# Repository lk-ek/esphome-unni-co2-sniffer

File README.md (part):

<!-- SPDX-FileCopyrightText: 2026 The esphome-unni-co2-sniffer contributors -->
<!-- SPDX-License-Identifier: GPL-3.0-or-later -->

# Unni CO₂ Smartification and Sensirion Gadget Bridge

ESPHome components and example firmware for two related sensor integrations:

- a Seeed Studio XIAO ESP32-C3 added to an Unni CO₂ monitor without taking control away from the original electronics; and
- a stationary, externally powered AHT21 room sensor, optionally combined with an ENS160, which reuses the same Sensirion/MyAmbience BLE and persistent-history implementation.

In the Unni build, the XIAO ESP32-C3 acts primarily as a **passive sniffer**:

- CO₂ is decoded from the existing I²C traffic between the Unni controller and the CO₂ module.
- Temperature and relative humidity are reconstructed from the existing RT/RH timing signals.
- Measurements are exposed to Home Assistant through ESPHome.
- The same measurements can be advertised over BLE in a Sensirion MyAmbience-compatible format.
- Optional persistent BLE history allows historical samples to be downloaded with MyAmbience.

The tested Unni monitor is sold as **CO2 Monitor Carbon Dioxide Detector 0601**, hence the orchestrator component name. BLE and history are provided by the separate reusable bridge:

```yaml
sensirion_gadget_bridge:
  id: unni_sensirion_bridge
  profile: trh_co2
  device_name: "Unni CO2 Monitor"

co2_monitor_0601:
  sensirion_bridge_id: unni_sensirion_bridge
```

The Unni integration was developed against one specific hardware revision. Other revisions should be verified before connecting the ESP.

---

## Supported devices

### Unni monitor

The passive in-monitor integration provides:

- passively decoded CO₂ concentration;
- reconstructed temperature and relative humidity;
- battery voltage and estimated battery state of charge;
- USB/VBUS presence;
- automatic USB/battery power policy and Light Sleep; and
- optional diagnostics and raw capture.

### Standalone room sensor

The stationary, externally powered integration provides:

- AHT21 temperature and relative humidity;
- optional ENS160 TVOC and AQI as Home Assistant-only air-quality measurements;
- SHT43-compatible BLE live data and persistent history; and
- no battery, VBUS or Unni capture subsystem.

ENS160 eCO₂ is deliberately not published. It is an algorithmic estimate, not the direct CO₂ measurement required by the `trh_co2` profile.

### Shared integrations

- ESPHome / Home Assistant
- Sensirion-compatible BLE live advertisements
- persistent BLE history with MyAmbience-compatible GATT download

### Unni-only power management

The following features belong to the Unni/XIAO integration:

- automatic distinction between USB and battery operation
- ESP32-C3 dynamic frequency scaling
- automatic Light Sleep in battery mode
- reduced BLE advertising rate on battery
- reduced Home Assistant publication rate on battery
- optional `Energy Save Mode` for measuring battery-style firmware behavior while physically powered through USB
- dedicated BLE-only measurement build without Wi-Fi or Home Assistant

### Unni diagnostics

Optional debug builds provide:

- RT/RH timing diagnostics
- I²C framing and decoder diagnostics
- raw I²C captures
- VCD conversion tools
- recovery diagnostics for occasionally missed GPIO edges

---

# Unni monitor integration

Everything in this section concerns the passive XIAO ESP32-C3 installation in
the Unni monitor or its future ESP32-C6 replacement PCB. The standalone room
sensor is documented separately below.

## ESP32-C6 Rev A PCB — work in progress

The [`unni-smartification-c6/`](unni-smartification-c6/) subtree contains a
dedicated four-layer ESP32-C6 hardware design with a replacement USB/power board
and a separate ESP/battery board. It keeps the original Unni connections as
T-taps and adds autonomous charging, USB/battery source isolation, native USB
and a hardware-inhibited forced-awake 5 V path.

> [!WARNING]
> This PCB is a **work in progress**. Placement and routing are not final, and
> the design has not replaced the currently tested XIAO ESP32-C3 installation.
> Reproducible schematic, connectivity, mechanical and system-level SPICE checks
> reduce design risk but do not constitute assembled-hardware validation.

The prototype PCBs for this project are kindly sponsored by
[PCBWay](https://www.pcbway.com/). Thank you to PCBWay for supporting the
project and helping turn the design into physical prototypes.

See the [ESP32-C6 Rev A project README](unni-smartification-c6/README.md) for
the power architecture, mechanics, current routing/fabrication status and
validation commands.

## XIAO ESP32-C3 wiring

| XIAO | GPIO | Unni connection | Purpose |
|---|---:|---|---|
| D1 | GPIO3 | RT | temperature timing signal |
| D2 | GPIO4 | RH | humidity timing signal |
| D4 | GPIO6 | CO₂ SDA | passive I²C data sniffing |
| D5 | GPIO7 | CO₂ SCL | passive I²C clock sniffing |
| D0 | GPIO2 / ADC1_CH2 | battery-divider midpoint | battery voltage |
| D3 | GPIO5 | VBUS-divider midpoint | USB power detection |
| 5V | — | Unni VBUS / 5 V | ESP supply |
| GND | — | Unni GND / battery − | common ground |

`RT` and `RH` are the PCB points associated with the temperature and humidity measurement circuitry.

The ESP must remain electrically passive with respect to the original signal paths.

The current tested installation uses **10 kΩ series resistors on each passive ESP tap**:

```text
Unni signal ---- 10 kΩ ---- XIAO GPIO
```

The resistors belong only in the ESP branches; do not insert them into the original Unni signal path. The RT/RH calibration is hardware-dependent, so calibration data collected with earlier direct or three/four-wire tap arrangements must not be mixed with the current two-wire/10 kΩ setup.

The RT/RH decoder now keeps separate temperature views: a diagnostic RT-model temperature, a dedicated Unni LCD-emulation curve, and a provisional external-reference Air Temperature curve. RH uses the RH-phase carrier period normalized by REF with temperature compensation. Air Temperature is the canonical temperature exported through Sensirion BLE/history when it is inside its validated envelope; the RT model is retained as a fallback outside that envelope. See `co2_monitor_0601/calibration.h` and the dated calibration notes under `docs/history/` for the coefficients and fit provenance.

---

## Battery voltage measurement

The tested circuit uses two 1 MΩ resistors:

```text
Battery + --- 1 MΩ ---+--- D0 / GPIO2
                      |
                     1 MΩ
                      |
Battery − / GND ------+

D0 / GPIO2 --- 0.1 µF --- GND
```

This produces a divider ratio of 2.0.

The firmware uses ESP-IDF ADC calibration, averaging and 12 dB attenuation.

Battery-related entities include:

- `Battery Voltage`
- `Battery Level`
- `Battery Runtime Estimate`
- `Battery Charge Time Estimate`
- `Battery Discharge Rate` (`%/h`, diagnostic when `debug_metrics: true`)
- `Battery Charge Rate` (`%/h`, diagnostic when `debug_metrics: true`)

`Battery Level` is a voltage-based Li-ion estimate. It is intentionally unavailable while physical USB power is present because charger-driven battery voltage is not a useful open-circuit state-of-charge measurement.

Debug builds intentionally limit the native ESPHome API to one simultaneous client while raw UDP capture is enabled. Home Assistant should keep that slot; use USB serial for live `esphome logs`. Additional native API log clients can consume enough heap on the ESP32-C3 to starve lwIP. If UDP export sees sustained `ENOMEM` pressure, the affected debug capture is dropped after repeated failures instead of retrying indefinitely and holding memory/network resources.

The runtime and charge-time estimates are learned from the observed voltage trend rather than from a fixed assumed current draw. Each USB/battery transition starts a new rate-estimator session, followed by a two-minute settling period. The short-term estimator then uses at least a five-minute observation window and exponentially smooths subsequent rate measurements. Until a meaningful trend is available, the corresponding estimate remains unavailable instead of publishing a speculative value.

Battery runtime also has a persistent self-learning layer. During battery operation the component accumulates real elapsed time and voltage-derived SOC drop. Once a session contains at least 2 hours and 8 percentage points of discharge, it can estimate an equivalent full-runtime value. A completed qualifying battery session is folded into the persistent model with a conservative EMA (25% new session / 75% previous model). The active session and learned model are checkpointed to flash every `battery_learning_save_interval` (default `30min`) and on session completion, so an overnight run or reboot does not discard the calibration data. The production `Battery Runtime Estimate` blends the persistent model with the recent discharge-rate estimate; before a learned model exists it behaves like the original recent-rate estimator.

With `debug_metrics: true`, `Battery Learned Full Runtime`, `Battery Learning Progress`, and `Battery Learning Cycles` expose the learning state. `Battery Learning Progress` reaches 100% when the current session has both at least 2 hours of data and at least 8 percentage points of SOC drop. The model intentionally learns effective runtime rather than claiming to measure true battery capacity in mAh; without a coulomb counter the voltage/SOC curve cannot provide that measurement reliably.

Battery-learning flash writes are logged after a successful synchronous commit.
Periodic checkpoints are labeled `periodic`, OTA-triggered force-saves are
labeled `OTA`, and end-of-session commits are labeled `session-end`, together
with the persisted SOC/session runtime/progress and learned-runtime state.

On battery, the estimator uses the normal voltage-derived SOC curve. With USB present, `Battery Level` stays unavailable and the charge estimator uses the charger-influenced battery-node voltage only as a charge-progress proxy. The charge ETA is therefore inherently less accurate, especially in the constant-voltage/taper region near full charge.

---

## USB/VBUS detection

The tested VBUS divider is:

```text
VBUS / 5 V --- 220 kΩ ---+--- D3 / GPIO5
                         |
                        220 kΩ
                         |
                        GND
```

The physical state is exposed as:

```text
USB Power
```

The reported value always reflects actual VBUS presence, even when the firmware is deliberately using the battery power policy through `Energy Save Mode`.

---

# Unni installation

## Minimal configuration

A minimal normal configuration is:

```yaml
esphome:
  name: i2csniffer

external_components:
  - source:
      type: local
      path: .

esp32:
  board: seeed_xiao_esp32c3
  framework:
    type: esp-idf

wifi:
  ssid: !secret wifi_ssid
  password: !secret wifi_password

api:
  encryption:
    key: !secret i2csniffer__encryption_key

sensirion_gadget_bridge:
  id: unni_sensirion_bridge
  profile: trh_co2

co2_monitor_0601:
  sensirion_bridge_id: unni_sensirion_bridge
```

The repository contains complete example configurations, so in normal use it is easier to start with one of those rather than build the YAML from scratch.

Build or flash with ESPHome:

```bash
esphome compile i2c-sniffer.yaml
esphome run i2c-sniffer.yaml
```

# Unni build variants

The repository contains these configurations for the Unni monitor:

| Configuration | Wi-Fi / HA | BLE | Debug capture | Purpose |
|---|---|---|---|---|
| `i2c-sniffer.yaml` | yes | yes | no | normal operation |
| `i2c-sniffer-debug.yaml` | yes | yes | yes | protocol/debugging work |
| `i2c-sniffer-no-ble.yaml` | yes | no | no | BLE power comparison |
| `i2c-sniffer-ble-only.yaml` | no | yes | no | BLE-only power measurement |
| `i2c-sniffer-sht43-probe.yaml` | yes | experimental | no | MyAmbience reverse engineering |

The SHT43 probe is diagnostic firmware and should not be used as the normal
Unni device identity.

---

# Unni Home Assistant entities

Home Assistant support is enabled by default:

```yaml
co2_monitor_0601:
  home_assistant: true
```

Omitting `home_assistant` is equivalent to setting it to `true`.

Only the dedicated BLE-only build intentionally uses:

```yaml
co2_monitor_0601:
  home_assistant: false
```

In that build the local ESPHome entity objects remain registered internally so ESPHome 2026.8 can derive its entity-vector sizes correctly, but the supplied YAML contains no `wifi:` or `api:` component, so they are not exposed to Home Assistant and cause no network traffic.

The normal `i2c-sniffer.yaml` build intentionally exposes only the production
measurement set plus operational power/battery controls:

The default Home Assistant names are intentionally concise: the physical-air `air_temperature` entity is shown as `Temperature`, and the physical carrier-based `rh_humidity` entity as `Humidity`.

- `CO2`
- `Temperature` (physical-air estimate)
- `Humidity` (physical carrier-based estimate)
- `Battery Voltage`
- `Battery Level`
- `Battery Runtime Estimate`
- `Battery Charge Time Estimate`
- `USB Power`
- `Energy Save Mode`
- `WiFi Home Assistant` when the runtime connectivity control is enabled
- `BLE Privacy` and `BLE Pairing Mode` while the experimental secure MyAmbience settings support is enabled

Sensor definitions may be customized:

```yaml
co2_monitor_0601:
  co2:
    name: "Living Room CO2"

  air_temperature:
    name: "Temperature"

  rh_humidity:
    name: "Humidity"
```

The shipped `i2c-sniffer-debug.yaml` sets `debug_metrics: true` and creates the
complete entity set as well: `RT Temperature`, both `Unni Display ...`
emulation entities, protocol error counters, raw timing/ratio metrics, battery
charge/discharge rates, quality and calibration/extrapolation flags. These are
not instantiated by the normal build.

# Unni component configuration

Useful options include:

```yaml
co2_monitor_0601:
  # Home Assistant
  home_assistant: true
  ha_publish_interval: 60s

  # Bridge composition and battery-specific BLE interval
  sensirion_bridge_id: unni_sensirion_bridge
  ble_battery_advertising_interval: 3s

  # Power management
  light_sleep: true
  light_sleep_max_awake: 10s
  co2_wake_idle_stable: 500ms
  co2_wake_guard_time: 500ms
  energy_save_mode_default: false
  energy_save_grace: 3s

  # Hardware
  rt_pin: 3
  rh_pin: 4
  co2_sda_pin: 6
  co2_scl_pin: 7
  battery_pin: 2
  battery_divider_ratio: 2.0
  battery_update_interval: 60s
  battery_learning_save_interval: 30min
  usb_power_pin: 5

  # Startup
  sniffer_start_delay: 10s

  # Diagnostics
  debug_metrics: false
  # Compiles main-loop stage timing and heap telemetry into the firmware.
  runtime_diagnostics: false
  # Optional ESP32-C3/C6 hardware assist. "gpio" keeps the pure ISR backend;
  # "rmt_scl" records SCL in RMT hardware and uses it only to repair strictly
  # protocol-invalid GPIO captures.
  i2c_capture_backend: gpio
  debug_capture: false
  # Experimental only: temporarily becomes an I2C master on a long-idle
  # LOW/LOW CO2 bus, using only the ESP32-C3 internal pull-ups through the
  # external 10 kOhm tap resistors.
  active_i2c_probe: false
  active_i2c_probe_interval: 60s
```

The defaults match the tested XIAO ESP32-C3 installation.

All configured GPIOs must be unique.

`rtrh_enabled`, `rtrh_edge_capture`, and `rtrh_decode_only` are mutually
exclusive capture modes. `rtrh_gpio_setup: true` is accepted only with one of
those modes; invalid combinations fail during YAML validation rather than
retrying GPIO setup at runtime.

`battery_pin` must be an ESP32-C3 ADC1-capable GPIO.

The Unni orchestrator configures its ESP-IDF power-management requirements;
the bridge configures the BLE server and persistent-history partition.

`active_i2c_probe` is intentionally disabled by default. It is a hardware diagnostic, not normal passive-sniffer operation. The probe runs only on battery policy after the CO2 bus has remained LOW/LOW and edge-free for at least one second. It first tries `0xEC05`; if no slave ACKs, it tries the observed `0x21B1` start command. Every attempt restores SDA/SCL to input-only/no-pull mode immediately afterwards. Do not enable it without series resistance on both CO2 tap lines.

---

# Unni USB and battery power policy

The firmware uses different runtime policies depending on physical power.

## USB power

Normal USB operation prioritizes responsiveness and reliability:

- automatic MCU Light Sleep is prevented
- CPU frequency is held at 80 MHz
- Wi-Fi power saving is disabled at runtime with `WIFI_PS_NONE`
- CO₂ I²C capture remains continuously enabled
- valid CO₂ measurements are published immediately
- valid RT temperature is published immediately; RH is published when its carrier timing also validates
- BLE advertisements use the USB interval, default `2s`

Because USB power is available, reducing ESP consumption is not the priority in this mode.

## Battery power

Battery operation prioritizes low average power:

- automatic Light Sleep is enabled
- GPIO3/GPIO4 RT/RH activity wakes the ESP
- CPU frequency is temporarily raised to 80 MHz while measurements are captured
- during a powered CO₂ measurement window the passive sniffer is active; after two plausible CO₂ observations it is gated off before the sensor rail collapses
- the expected slow SCL/SDA shutdown decay is ignored with the I²C interrupts disabled, avoiding large garbage captures and ISR storms
- after the dead bus has remained LOW/LOW for `co2_wake_idle_stable` (default `500ms`) plus `co2_wake_guard_time` (default `500ms`), GPIO7/SCL HIGH is armed as the next CO₂ power-up wake source
- a real CO₂ power-up disarms GPIO7 wake and re-enables the passive sniffer before the native measurement transaction; GPIO6 remains passive
- after the RT/RH wake window is complete, the ESP may return to Light Sleep
- Wi-Fi uses `WIFI_PS_MIN_MODEM`
- Home Assistant publication is throttled to the latest values, default once per minute
- BLE advertisements use the battery interval, default `3s`

The corresponding options are:

```yaml
sensirion_gadget_bridge:
  id: unni_sensirion_bridge
  advertising_interval: 2s

co2_monitor_0601:
  sensirion_bridge_id: unni_sensirion_bridge
  light_sleep: true
  light_sleep_max_awake: 10s
  co2_wake_idle_stable: 500ms
  co2_wake_guard_time: 500ms
  ha_publish_interval: 60s
  ble_battery_advertising_interval: 3s
```

---

# Unni Energy Save Mode

`Energy Save Mode` exists mainly for controlled power measurements.

When enabled while the hardware is still physically powered from USB, the component behaves as if USB power were absent.

This allows a USB power meter to compare normal firmware behavior against the battery-oriented runtime policy without changing the electrical power source.

The physical `USB Power` entity remains truthful.

In Energy Save Mode:

- automatic Light Sleep is enabled
- the battery capture-window policy is used
- Wi-Fi uses `WIFI_PS_MIN_MODEM`
- BLE uses the battery advertising interval
- Home Assistant publication uses the battery throttle

The default is:

```yaml
co2_monitor_0601:
  energy_save_mode_default: false
  energy_save_grace: 3s
```

The grace period keeps the normal USB power locks briefly after the HA switch is enabled so that the state change can propagate before automatic Light Sleep becomes active.

Native USB Serial/JTAG may become unavailable while automatic Light Sleep is active. This does not affect the ESP32-C3 ROM USB bootloader, so USB flashing remains possible.

---

# Unni BLE-only measurement build

`i2c-sniffer-ble-only.yaml` is intended for measuring the cost of BLE without Wi-Fi/API overhead.

It intentionally contains no:

- `wifi:`
- `api:`
- captive portal
- OTA

It keeps:

- sensor decoding
- BLE live data
- BLE history
- power management

The relevant configuration is:

```yaml
sensirion_gadget_bridge:
  id: unni_sensirion_bridge
  profile: trh_co2
  ble: true
  ble_live: true
  ble_history: true

co2_monitor_0601:
  sensirion_bridge_id: unni_sensirion_bridge
  home_assistant: false
  energy_save_mode_default: true
  energy_save_grace: 0s
```

Flash this build over USB.

Recent example measurements on the tested hardware were approximately:

| Mode | Average power |
|---|---:|
| normal Wi-Fi + HA + BLE | 2.84 mW |
| Energy Save Mode | 2.07 mW |
| BLE-only | 1.34 mW |

These measurements were made with a USB power meter and should be treated as comparative rather than laboratory-grade absolute values.

Avoid running `ping`, `esphome logs`, an actively polling web UI or other unnecessary network traffic during power measurements.

---

# Standalone room sensor integration

This is a stationary, externally powered AHT21 room sensor. An ENS160 may be
fitted for additional Home Assistant air-quality data. The existing
`mobilesensor-*.yaml` filenames are retained for compatibility, but “mobile
sensor” is not used here as the device description because the hardware has no
battery operating mode.

It uses `sensirion_gadget_bridge` directly and does not instantiate
`co2_monitor_0601`. Consequently it has no Unni GPIO capture, battery ADC,
battery learning, VBUS detection, Energy Save Mode or automatic Light-Sleep
policy.

## Hardware

The shipped configurations target `wemos_d1_mini32` and use one 100 kHz I²C
bus:

| GPIO | Device | Address | Purpose |
|---:|---|---:|---|
| GPIO23 | AHT21 and optional ENS160 | `0x38` / `0x53` | SDA |
| GPIO19 | AHT21 and optional ENS160 | `0x38` / `0x53` | SCL |

No battery divider, VBUS input or Unni signal tap is part of this configuration.

## Configuration

```yaml
sensirion_gadget_bridge:
  id: sensirion_bridge
  profile: sht43_trh
  temperature_id: aht21_temp
  humidity_id: aht21_humi
  history_time_id: room_sensor_wall_clock
  ble: true
  ble_live: true
  ble_history: true
  advertising_interval: 2s
```

Use `mobilesensor-sensirion.yaml` when an ENS160 is fitted, or
`mobilesensor-sensirion-no-ens160.yaml` for AHT21-only hardware. Both variants
provide the same AHT21 BLE identity, live data, persistent history, OTA flush
and MyAmbience GATT behavior.

The bridge coalesces sequential AHT21 temperature and humidity callbacks for
100 ms. A restarted coalescing window publishes the newest complete pair rather
than two partially updated samples.

## Home Assistant and ENS160

Both variants expose AHT21 temperature and humidity. The ENS160 variant also
exposes TVOC, AQI and an `ENS160` control switch. It starts off after every
boot. Enabling it wakes the sensor before polling resumes; disabling it suspends
polling before Deep Sleep and publishes TVOC/AQI as unavailable.

AHT21 compensation remains enabled for ENS160 operation. Heating from an active
ENS160 may influence the nearby AHT21; no unvalidated correction curve is
applied. TVOC and AQI never participate in BLE sample completeness, GATT or
history. ENS160 eCO₂ is exposed nowhere. Switching the ENS160 on or off cannot
pause, clear or reset AHT21 history.

---

# Shared Sensirion bridge

## Architecture and sample ownership

BLE and history consume one authoritative, profile-aware sample owned by
`sensirion_gadget_bridge`:

```yaml
sensirion_gadget_bridge:
  id: unni_sensirion_bridge
  profile: trh_co2       # or sht43_trh
  ble: true
  ble_live: true
  ble_history: true
  device_name: "Unni CO2 Monitor"
  identity_mode: device_derived
  advertising_interval: 2s
  history_time_id: unni_wall_clock
```

For `sht43_trh`, `temperature_id` and `humidity_id` may bind the bridge directly
to ESPHome sensors. They must be configured together.
`sht43_identity_probe: true` remains a compatibility alias for this profile;
contradictory profile and alias settings are rejected.

| Concern | Unni monitor | Standalone room sensor |
|---|---|---|
| Measurement producer | passive CO₂ and RT/RH decoders | AHT21 state callbacks |
| Bridge profile | `trh_co2` | `sht43_trh` |
| Complete sample | finite T/RH plus valid CO₂ | finite T/RH; CO₂ remains unset |
| History guard | Unni capture-aware guard | generic transfer watchdogs only |
| Optional air quality | none | ENS160 TVOC/AQI in HA only |
| Power policy | USB/battery orchestration | externally powered; no Unni policy |

Invalid or out-of-range input does not replace the last valid sample. BLE live
data, SHT43 GATT temperature/humidity and history all read the same accepted
sample, preventing different paths from applying different completeness rules.
The first complete sample is immediately eligible for history; subsequent
samples follow the configured history interval. Existing flash layout and GATT
history wire format are shared by both producers.

## Sensirion / MyAmbience compatibility

The normal Unni firmware advertises temperature, humidity and CO₂ in a Sensirion Gadget/MyAmbience-compatible format. The standalone room-sensor profile advertises SHT43-style temperature and humidity only.
For the temperature field it uses `Air Temperature` inside the externally validated air-temperature envelope, falling back to the diagnostic RT model only when that physical-air estimate is unavailable. BLE humidity remains the physical carrier-based `RH Humidity`; the Unni display-emulation values are never advertised as physical measurements.

The reusable bridge is composed with the Unni orchestrator in the shipped BLE
YAMLs. The name shown for the normal MyCO2 gadget is configured on that bridge:

```yaml
sensirion_gadget_bridge:
  id: unni_sensirion_bridge
  profile: trh_co2
  device_name: "Unni CO2 Monitor"

co2_monitor_0601:
  sensirion_bridge_id: unni_sensirion_bridge
```

`device_name` defaults to `Unni CO2 Monitor` for the `trh_co2` profile and to `SHT43 DB` for the `sht43_trh` profile. It is limited to 31 bytes to match the Sensirion `AlternativeDeviceName` characteristic. It sets the normal Device Information model name and the default `AlternativeDeviceName`. A name explicitly changed through the Device Settings service remains persistent. The compatibility-sensitive GAP/local identity remains `S` and is intentionally not changed by this option. The old `ble_device_name` key remains on the Unni compatibility surface.

Bridge `identity_mode` defaults to `device_derived` and therefore needs no YAML
configuration. It derives a stable, locally administered Bluetooth address and
Device ID from the ESP eFuse MAC so multiple monitors do not collide.
`legacy_fixed` remains available only as an explicit compatibility override for
installations that must retain the old fixed identity. Changing identity can
invalidate existing bonds and MyAmbience caches and may require opening Pairing
Mode once in Home Assistant.

The GAP name used by the normal compatibility mode is:

```text
S
```

The Device Information Service identifies the manufacturer as:

```text
Gadget
```

The firmware does not claim that the hardware was manufactured by Sensirion.

The BLE compatibility implementation is local code using ESPHome and ESP-IDF BLE APIs. The production firmware does not directly vendor or link the Sensirion Gadget BLE Arduino Library or Sensirion UPT Core.

Parts of the protocol implementation were developed with reference to Sensirion's published software. See:

- [THIRD_PARTY_NOTICES.md](THIRD_PARTY_NOTICES.md)
- `LICENSES/`

for attribution, provenance and upstream license texts.

---

## Persistent BLE history

Advertising after GATT disconnects is reasserted deterministically so ESPHome's automatic advertiser restart cannot replace the Sensirion manufacturer-data payload. The Device Settings privacy flag (`IsAdvertiseDataEnabled`) is persistent and is logged explicitly at startup.

With:

```yaml
sensirion_gadget_bridge:
  ble_history: true
```

samples are stored in the `senshist` flash partition.

MyAmbience can download the history through the compatible GATT protocol.

The history ring is persistent across normal reboots.

The 4096-sample history is flash-backed. Only a small pending write ring is kept in RAM, so enabling MyAmbience history does not require a second 32 KiB in-memory copy of the persistent sample store. When a continuous run exceeds 4096 samples, the sparse time anchor advances with each ring eviction; restored history therefore still timestamps the retained 4096-sample window rather than the already-overwritten beginning of the run.

History metadata uses a redundant version-4 A/B journal in the first and last
sectors of the 64 KiB partition; the 14 data sectors and 8-byte sample wire
layout are unchanged. Version-2/3 metadata is read in place and migrated on the
next metadata flush. V4 uses the two formerly reserved metadata words for a
sparse wall-clock anchor and the sample count of the newest continuous run. The
anchor is created only when a run starts after a reboot/cadence gap, when the
wall clock first becomes valid, or after a material wall-clock correction; it is
not stored per sample. API-enabled variants obtain UTC from Home Assistant. The
BLE-only build has no wall-clock source and therefore starts a new relative run
after reboot rather than inventing timestamps. Failed metadata writes remain
dirty and are retried. A client may select only intervals from 60 seconds
through 24 hours. Changing the interval clears history incrementally from the
main loop (at most one sector erase per loop), while sampling and download
remain paused.

The official Sensirion download format has one header with one interval and one
`age-of-latest-sample`, so it cannot describe gaps inside a single transfer.
The bridge therefore keeps runs separate on the wire. The first download sends
the newest continuous run (or its newest requested subset). Each subsequently
completed download within a rolling five-minute session sends the next older
continuous run; completion resets the five-minute timer. Disconnecting does not
reset the cursor, while an aborted transfer does not advance it. Once the timer
expires, the next download starts again at the newest run. The history-count
characteristic follows the same cursor so MyAmbience sees the size of the run it
will receive next.

Completed-run boundaries are persisted sparsely in ESPHome NVS: one 8-byte
record per gap containing the run's UTC anchor, sample count and physical flash
start slot. No timestamp is added to ordinary samples and the Sensirion sample
or download wire formats are unchanged. Up to 128 completed-run descriptors are
retained; descriptors whose samples have already fallen out of the 4096-sample
flash window are ignored. Runs without a trustworthy wall-clock anchor are not
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
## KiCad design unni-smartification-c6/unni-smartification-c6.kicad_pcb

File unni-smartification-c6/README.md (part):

# Unni CO2 Smartification — ESP32-C6 Rev A

Target: **KiCad 10.99 nightly or newer**. The current manufacturing master uses a 4-layer stackup and native KiCad 10.99 geometric constraints.

This repository contains two physical PCBs in one KiCad PCB file so cross-board connectivity remains visible while routing. Placement and routing are still work in progress; the schematic and power architecture are substantially defined and covered by reproducible connectivity/SPICE checks.

## PCB sponsorship

The prototype PCBs for this project are kindly sponsored by [PCBWay](https://www.pcbway.com/). A big thank-you to PCBWay for supporting the project and helping turn the design into real hardware.

## Hardware overview

The images below are generated directly from the current KiCad project with `kicad-cli`; they are not hand-maintained screenshots. The two physical boards intentionally remain in one PCB file during design so their interconnect nets can be routed and validated together.

### PCB — component side

The long, narrow board on the left is the **USB / power board**. The larger board on the right is the **ESP / battery board**. The USB board carries the forced-awake 5 V power stage and the enclosure-specific USB interface, while the ESP board carries the charger, 3.3 V supply, ESP32-C6 and the sensor/control interfaces.

For placement and routing inspection, the orthographic top view is also useful:

### PCB — back side

The USB-C receptacle is deliberately a **back-side component** because the mechanical measurements describe the rear side of the original enclosure. Only the measured 19 x 18 mm rear clearance area may contain back-side components; the rest of that board lies against the enclosure. A footprint without an installed 3D model will naturally not appear in these renders even though its pads and board placement are present in KiCad.

### Schematics

#### USB, forced-awake boost and Unni power interface

#### ESP32-C6, charger, 3.3 V regulator and auxiliary interfaces

The simulation harness is intentionally not shown here because it is not part of the manufactured hardware. Its generated image remains available at `docs/images/schematic/simulation-harness.png` for debugging.

### Power sequencing and source handover

There are two independent questions in the power architecture: **how the ESP stays alive**, and **whether the Unni is being fed 5 V so that it behaves as USB-powered rather than entering its battery energy-save mode**.

**1. USB disconnected, normal battery operation.** The protected 1S Li-ion feeds `+BATT`. The discrete load-share path connects the battery to `SYS`, and the TPS63031 generates the regulated `+3V3` rail for the ESP32-C6. The Unni can continue to run from its own battery/DC input without needing the ESP-generated 5 V path. This is the low-power baseline state.

**2. ESP requests forced-awake operation while USB is absent.** Once the ESP is alive from `+3V3`, it may assert `BOOST_CMD`. The hardware-enable network then allows the TPS613222A 5 V boost stage on the USB/power board to run from `+BATT`. Its `+5V` output reaches `UNNI_AC` through the output Schottky diode. Electrically, the Unni now sees the same AC/VBUS-style 5 V condition it would see from USB, so firmware can deliberately pull the Unni out of its battery energy-save behavior.

**3. Real USB is plugged in.** `VBUS` immediately supplies `SYS` through the Schottky/load-share path, so the TPS63031 and ESP are powered from USB rather than discharging the cell. In parallel, the MCP73831 charges `+BATT` at the resistor-programmed current, and the ESP can observe `CHARGE_STAT` as well as the filtered `USB_ADC` divider. USB VBUS also feeds `UNNI_AC` directly through its own Schottky path.

**4. USB always wins over the battery-generated 5 V path.** The forced-awake boost has a hardware VBUS inhibit. When real `VBUS` is present, the MOSFET inhibit network prevents the TPS613222A path from being enabled even if firmware leaves `BOOST_CMD` asserted or crashes in the wrong state. The two 5 V sources therefore do not intentionally drive each other. The output diodes provide the final source isolation at `UNNI_AC`.

**5. USB is removed again.** The charger stops, the battery load-share path retakes `SYS`, and the TPS63031 keeps the ESP on `+3V3` across the source transition. The forced-awake 5 V rail remains off unless firmware explicitly requests it after USB has disappeared. This separation is important: keeping the ESP alive does not automatically force the Unni into its higher-power USB mode.

The practical state table is therefore:

| External USB | `BOOST_CMD` | ESP source | Unni `UNNI_AC` | Result |
| --- | --- | --- | --- | --- |
| absent | 0 | battery -> `SYS` -> TPS63031 | no ESP-generated 5 V | normal battery / energy-save capable |
| absent | 1 | battery -> `SYS` -> TPS63031 | TPS613222A -> `+5V` -> diode | forced-awake / USB-like Unni power state |
| present | 0 | VBUS -> `SYS` -> TPS63031 | VBUS -> diode | USB-powered; battery charging |
| present | 1 | VBUS -> `SYS` -> TPS63031 | VBUS -> diode; boost hardware-inhibited | same safe USB-powered state |

The ADC paths (`BAT_ADC`, `USB_ADC`, `BACKLIGHT_ADC`) and `CHARGE_STAT` let firmware distinguish these power states without making the safety-critical source arbitration depend on software alone.

### Re-generating the README images

With a KiCad 10.99 nightly `kicad-cli` on `PATH`, run:

```sh
./tools/render_readme_assets.sh
```

Or point it at a specific build:

```sh
KICAD_CLI=/path/to/kicad-cli ./tools/render_readme_assets.sh
```

This refreshes all PCB renders and schematic PNGs under `docs/images/`.

## Physical boards

- **USB / power board** — 19 mm fixed width, 1.0 mm finished-board target, USB-C on B.Cu at the measured enclosure datum. It contains USB-C/CC, the TPD2E009DBZR USB ESD shunt, the battery-driven 5 V forced-awake boost and the Unni AC/DC interface.
- **ESP / battery board** — maximum 46 x 32 mm. It contains the ESP32-C6-MINI-1, MCP73831 charger and USB/battery load sharing, TPS63031 3.3 V buck-boost, battery/USB/backlight ADCs, battery NTC, CO2/RT/RH taps, touch emulation, and local service controls.

The boards currently use JST-PH connectors where serviceability is useful. If enclosure clearance proves too tight, their exposed through-hole/SMT pads are also suitable for direct wire soldering; this is an assembly fallback, not a separate electrical architecture.

The 3-pin auxiliary connector **J5** is ordered **pin 1 = `CONN_TOUCH`, pin 2 = `CONN_LED+`, pin 3 = `CONN_BTN`**. `CONN_BTN` goes to ESP32-C6 IO22 (module pin 28); the touch-emulation path couples Q10 to `CONN_TOUCH` through populated C32 = 220 pF.

## Power architecture

```text
USB VBUS ──────────────┬─ MCP73831 (≈196 mA, RPROG=5.1k) ── +BATT
                       ├─ Schottky ── SYS ── TPS63031 ── +3V3 ── ESP32-C6
                       └─ Schottky ─────────────────────── UNNI_AC

protected 1S Li-ion ─ +BATT ─ PMOS load share ─────────── SYS
                    └ +BATT ─ boost switch ─ TPS613222A ─ +5V ─ Schottky ─ UNNI_AC
```

Hardware VBUS inhibit prevents the battery 5 V boost from being enabled while real USB power is present. The battery pack used by the design contains its own protection PCB.

## USB

- USB-C sink: independent 5.1 kΩ Rd on CC1 and CC2.
- Native ESP32-C6 USB Full-Speed is routed through 22 Ω series resistors near the ESP.
- USB ESD: **TI TPD2E009DBZR**, a two-line ground-referenced shunt device with no VBUS/VCC rail. This avoids a clamp path that could back-power VBUS and interfere with the hardware boost inhibit.
- `USB_ADC` includes local RC filtering.
- USB differential geometry is intentionally **not final yet**. Route it only after the selected PCBWay stackup is loaded; final impedance geometry should be checked against PCBWay's impedance/stackup data if controlled impedance is ordered.

## 4-layer PCBWay stackup

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
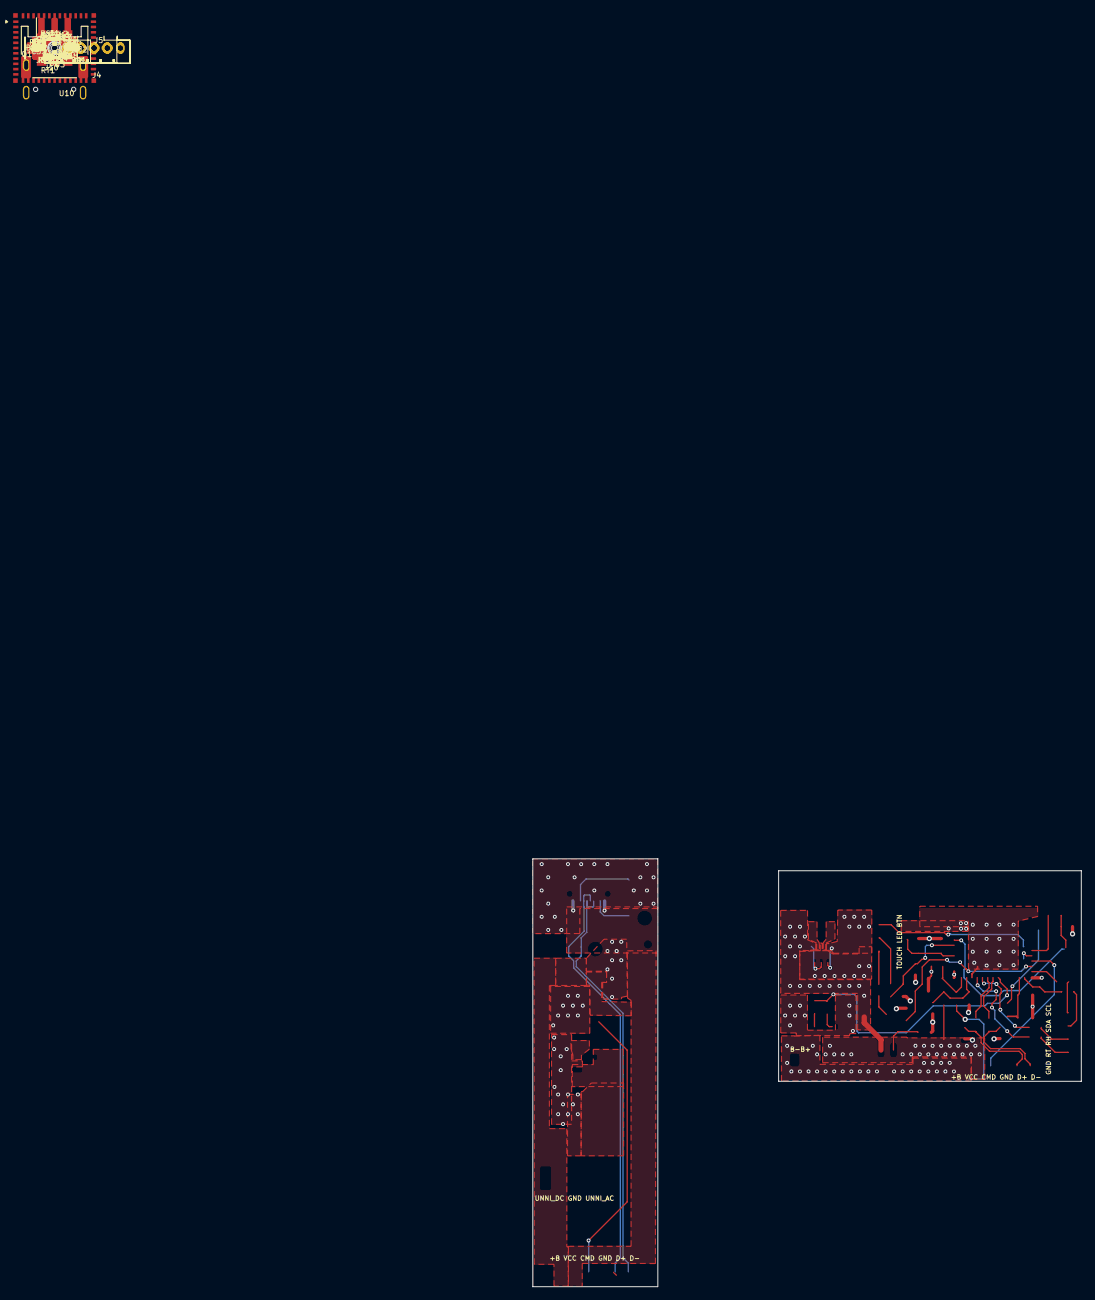
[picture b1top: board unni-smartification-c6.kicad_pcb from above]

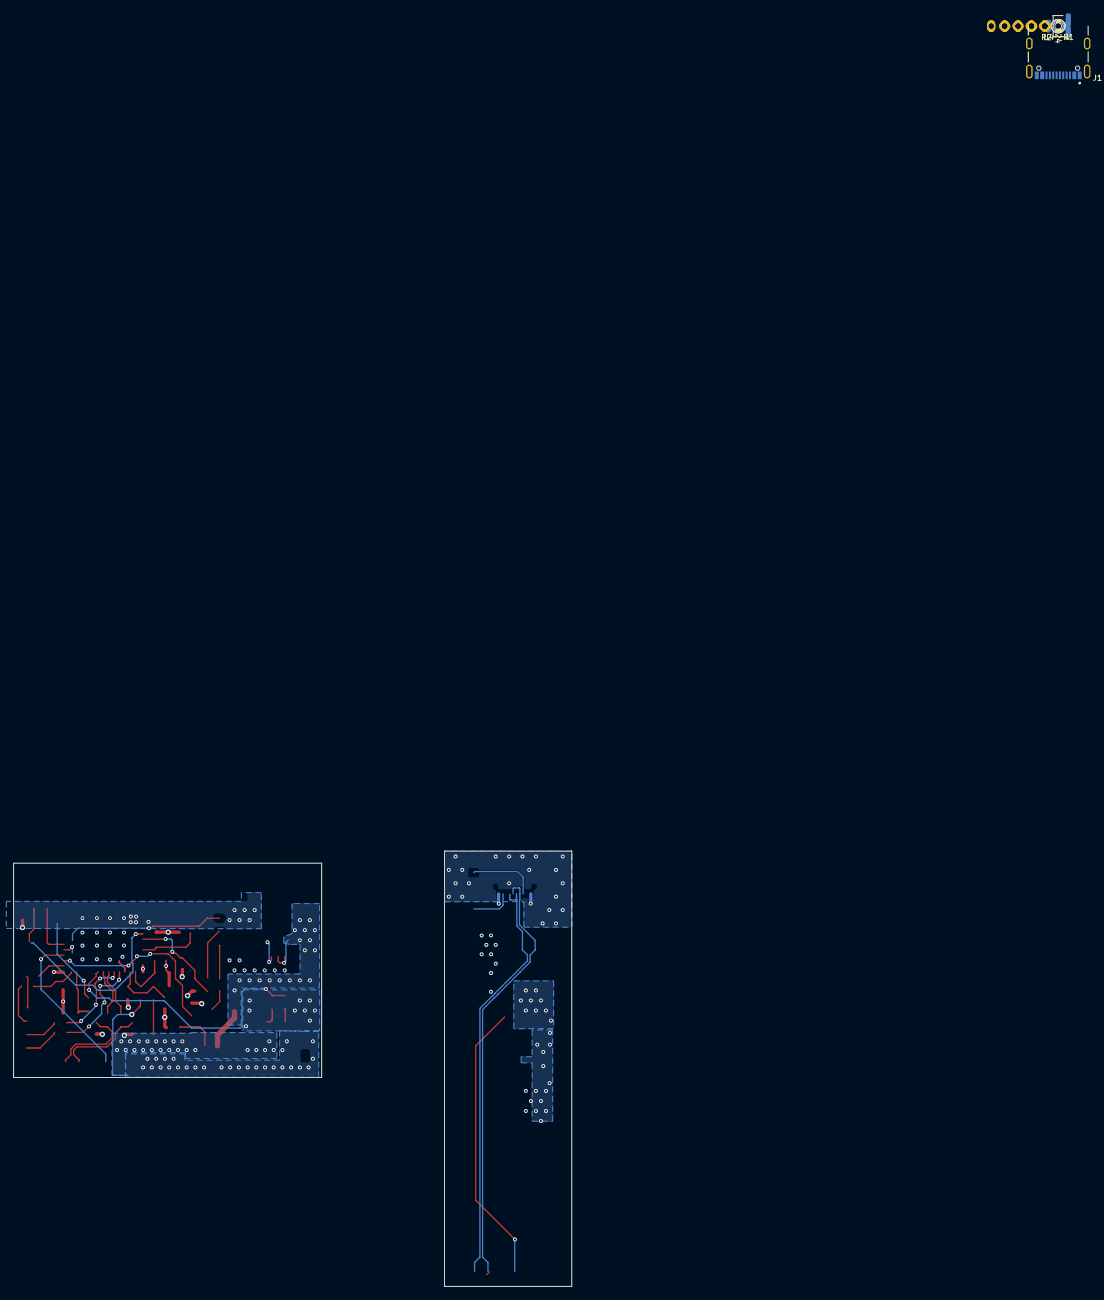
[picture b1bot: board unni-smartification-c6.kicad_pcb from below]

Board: 4 copper layers, 75 parts (5 on the bottom side), 45 nets.

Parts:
C1, C2: 4.7uF; C_0805_2012Metric_Pad1.18x1.45mm_HandSolder
C3, C5, C6, C7: 10uF; C_0805_2012Metric_Pad1.18x1.45mm_HandSolder
C4, C11, C20, C21, C22: 100nF; C_0603_1608Metric_Pad1.08x0.95mm_HandSolder
C8: 22uF; C_0805_2012Metric_Pad1.18x1.45mm_HandSolder
C9: 1uF; C_0603_1608Metric_Pad1.08x0.95mm_HandSolder
C10: 10uF; C_0603_1608Metric_Pad1.08x0.95mm_HandSolder
C12, C13: 22pF DNP; C_0603_1608Metric_Pad1.08x0.95mm_HandSolder
C32: 220pF; C_0603_1608Metric_Pad1.08x0.95mm_HandSolder
C33: 10nF DNP; C_0603_1608Metric_Pad1.08x0.95mm_HandSolder
D1, D3, D4: SS14; D_SMA_Handsoldering
H1: NPTH_2mm; USB_LEFT_MOUNT_D2.0
H2: NPTH_1mm; USB_LEFT_SMALL_D1.0
H3: NPTH_2mm; USB_CENTER_MOUNT_D2.0
H4: NPTH_1.5mm; USB_RIGHT_HOLE_D1.5
J1: UJ20-C-H-G-SMT-1-P16-TR; SAMESKY_UJ20-C-H-G-SMT-1-P16-TR
J2: B2B-PH-K-S; JST_PH_B2B-PH-K_1x02_P2.00mm_Vertical
J3, J10: B6B-PH-K-S; JST_PH_B6B-PH-K_1x06_P2.00mm_Vertical
J4: S3B-PH-SM4-TB; JST_PH_S3B-PH-SM4-TB_1x03-1MP_P2.00mm_Horizontal
J5: B3B-PH-K-S; JST_PH_B3B-PH-K_1x03_P2.00mm_Vertical
J6: B5B-PH-K-S; JST_PH_B5B-PH-K_1x05_P2.00mm_Vertical
L1: 2.2uH; L_Murata_LQH3NPN_3.0x3.0mm_HandSolder
L2: 2.2uH; L_Murata_DFE322520FD_3.2x2.5mm_HandSolder
Q1, Q2: AO3401A; SOT-23_Handsoldering
Q3, Q4, Q10: AO3400A; SOT-23_Handsoldering
R1, R2, R3: 5.1k; R_0805_2012Metric_Pad1.20x1.40mm_HandSolder
R5, R52: 100k; R_0805_2012Metric_Pad1.20x1.40mm_HandSolder
R6, R7, R9, R30, R31: 1M; R_0805_2012Metric_Pad1.20x1.40mm_HandSolder
R8, R20, R21, R34: 10k; R_0805_2012Metric_Pad1.20x1.40mm_HandSolder
R11: 150k; R_0805_2012Metric_Pad1.20x1.40mm_HandSolder
R12, R32, R33, R51: 220k; R_0805_2012Metric_Pad1.20x1.40mm_HandSolder
R13: 47k; R_0805_2012Metric_Pad1.20x1.40mm_HandSolder
R22, R23: 22R; R_0805_2012Metric_Pad1.20x1.40mm_HandSolder
R24: 10K; R_0603_1608Metric_Pad0.98x0.95mm_HandSolder
R40, R41, R42, R43: 10k; R_0603_1608Metric_Pad0.98x0.95mm_HandSolder
R50: 330k; R_0805_2012Metric_Pad1.20x1.40mm_HandSolder
RT1: NTCC-10K; JST_PH_B2B-PH-K_1x02_P2.00mm_Vertical
SW1: RST; SW_Jianfu_TVAF36-N014JW-R_HandSolder
SW2: BOOT; SW_Jianfu_TVAF36-N014JW-R_HandSolder
U1: MCP73831; SOT-23-5_HandSoldering
U2: TPS63031; WSON-10-1EP_2.5x2.5mm_P0.5mm_EP1.2x2mm
U3: TPS613222ADBV; SOT-23-5
U4: TPD2E009DBZR; SOT-23_Handsoldering
U10: ESP32-C6-MINI-1-N4; ESP32-C6-MINI-1

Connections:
+3V3: C5.1, C6.1, C10.1, C11.1, R20.1, R21.1, U2.1 (VOUT), U2.10 (FB), U10.3 (3V3)
+5V: C8.1, D4.2 (A), U3.4 (VOUT)
+BATT: C2.1, J2.2, J3.6, J4.1, J10.6, Q1.3 (D), Q2.2 (S), R7.2, R30.1, U1.3 (V_{BAT})
/ESP32-C6 + Auxiliary/BOOT_GPIO9: R21.2, SW2.2, U10.23 (IO9)
/ESP32-C6 + Auxiliary/ESP_EN: R20.2, SW1.2, U10.8 (EN)
/ESP32-C6 + Auxiliary/USB_N: R22.1, U10.17 (IO12)
/ESP32-C6 + Auxiliary/USB_P: R23.1, U10.18 (IO13)
/USB + Power/BOOST_IN: C7.1, L2.1, Q2.3 (D)
BACKLIGHT_ADC: C33.1, R50.2, R51.1, U10.6 (IO3)
BAT_ADC: C20.1, R30.2, R31.1, U10.12 (IO0)
BAT_TEMP_ADC: C21.1, R34.2, RT1.1, U10.5 (IO2)
BAT_TEMP_EXCITE: R34.1, U10.29 (IO23)
BOOST_CMD: J3.4, J10.4, R8.1, U10.27 (IO21)
CHARGE_STAT: R11.2, R12.1, U10.19 (IO14)
CO2_SCL: R41.2, U10.25 (IO19)
CO2_SDA: R40.2, U10.24 (IO18)
CONN_BTN: J5.3, R24.2
CONN_LED+: J5.2, R50.1
CONN_RH: J6.3, R43.1
CONN_RT: J6.4, R42.1
CONN_SCL: J6.1, R41.1
CONN_SDA: J6.2, R40.1
CONN_TOUCH: C32.1, J5.1
GND: C1.2, C2.2, C3.2, C4.2, C5.2, C6.2, C7.2, C8.2, C9.2, C10.2, C11.2, C12.2, C13.2, C20.2, C21.2, C22.2, C33.2, J1.A1_B12 (GND), J1.B1_A12 (GND__1), J1.SH1 (SHIELD), J1.SH2 (SHIELD__1), J1.SH3 (SHIELD__2), J1.SH4 (SHIELD__3), J2.1, J3.3, J4.2, J6.5, J10.3, Q3.2 (S), Q4.2 (S), Q10.2 (S), R1.2, R2.2, R3.2, R6.1, R9.2, R12.2, R13.1, R31.2, R33.2, R51.2, R52.2, RT1.2, SW1.1, SW2.1, U1.2 (V_{SS}), U2.3 (PGND), U2.7 (PS/SYNC), U2.9 (GND), U2.11 (PGND), U3.2 (GND), U4.3 (GND), U10.1 (GND), U10.2 (GND), U10.11 (GND), U10.14 (GND), U10.36 (GND), U10.37 (GND), U10.38 (GND), U10.39 (GND), U10.40 (GND), U10.41 (GND), U10.42 (GND), U10.43 (GND), U10.44 (GND), U10.45 (GND), U10.46 (GND), U10.47 (GND), U10.48 (GND), U10.49 (GND), U10.50 (GND), U10.51 (GND), U10.52 (GND), U10.53 (GND)
unnamed: J1.A5 (CC1), R1.1
unnamed: J1.B5 (CC2), R2.1
unnamed: Q1.1 (G), R5.2, R6.2
unnamed: Q2.1 (G), Q3.3 (D), R7.1
unnamed: Q3.1 (G), Q4.3 (D), R8.2, R9.1
unnamed: C32.2, Q10.3 (D)
unnamed: R3.1, U1.5 (PROG)
unnamed: R11.1, U1.1 (STAT)
unnamed: L1.1, U2.4 (L1)
unnamed: L1.2, U2.2 (L2)
unnamed: L2.2, U3.1 (SW)
unnamed: R24.1, U10.28 (IO22)
RH: R43.2, U10.16 (IO7)
RT: R42.2, U10.15 (IO6)
SYS: C3.1, C4.1, D1.1 (K), Q1.2 (S), U2.5 (VIN), U2.6 (EN), U2.8 (VINA)
TOUCH_TRIGGER: Q10.1 (G), R52.1, U10.26 (IO20)
UNNI_AC: C9.1, D3.1 (K), D4.1 (K), J4.3
USB_ADC: C22.1, R32.2, R33.1, U10.13 (IO1)
USB_RAW_N: C12.1, J1.A7 (DN1), J1.B7 (DN2), J3.2, J10.2, R22.2, U4.2 (D-)
USB_RAW_P: C13.1, J1.A6 (DP1), J1.B6 (DP2), J3.1, J10.1, R23.2, U4.1 (D+)
VBUS: C1.1, D1.2 (A), D3.2 (A), J1.A4_B9 (VBUS), J1.B4_A9 (VBUS__1), J3.5, J10.5, Q4.1 (G), R5.1, R13.2, R32.1, U1.4 (V_{DD})

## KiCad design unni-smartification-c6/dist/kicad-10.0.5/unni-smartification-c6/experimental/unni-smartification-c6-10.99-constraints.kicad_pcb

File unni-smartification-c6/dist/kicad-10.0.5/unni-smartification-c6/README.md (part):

# Unni CO2 Smartification — ESP32-C6 Rev A

Target: **KiCad 10.99 nightly or newer**. The current manufacturing master uses a 4-layer stackup and native KiCad 10.99 geometric constraints.

This repository contains two physical PCBs in one KiCad PCB file so cross-board connectivity remains visible while routing. Placement and routing are still work in progress; the schematic and power architecture are substantially defined and covered by reproducible connectivity/SPICE checks.

## Hardware overview

The images below are generated directly from the current KiCad project with `kicad-cli`; they are not hand-maintained screenshots. The two physical boards intentionally remain in one PCB file during design so their interconnect nets can be routed and validated together.

### PCB — component side

The long, narrow board on the left is the **USB / power board**. The larger board on the right is the **ESP / battery board**. The USB board carries the forced-awake 5 V power stage and the enclosure-specific USB interface, while the ESP board carries the charger, 3.3 V supply, ESP32-C6 and the sensor/control interfaces.

For placement and routing inspection, the orthographic top view is also useful:

### PCB — back side

The USB-C receptacle is deliberately a **back-side component** because the mechanical measurements describe the rear side of the original enclosure. Only the measured 19 x 18 mm rear clearance area may contain back-side components; the rest of that board lies against the enclosure. A footprint without an installed 3D model will naturally not appear in these renders even though its pads and board placement are present in KiCad.

### Schematics

#### USB, forced-awake boost and Unni power interface

#### ESP32-C6, charger, 3.3 V regulator and auxiliary interfaces

The simulation harness is intentionally not shown here because it is not part of the manufactured hardware. Its generated image remains available at `docs/images/schematic/simulation-harness.png` for debugging.

### Power sequencing and source handover

There are two independent questions in the power architecture: **how the ESP stays alive**, and **whether the Unni is being fed 5 V so that it behaves as USB-powered rather than entering its battery energy-save mode**.

**1. USB disconnected, normal battery operation.** The protected 1S Li-ion feeds `+BATT`. The discrete load-share path connects the battery to `SYS`, and the TPS63031 generates the regulated `+3V3` rail for the ESP32-C6. The Unni can continue to run from its own battery/DC input without needing the ESP-generated 5 V path. This is the low-power baseline state.

**2. ESP requests forced-awake operation while USB is absent.** Once the ESP is alive from `+3V3`, it may assert `BOOST_CMD`. The hardware-enable network then allows the TPS613222A 5 V boost stage on the USB/power board to run from `+BATT`. Its `+5V` output reaches `UNNI_AC` through the output Schottky diode. Electrically, the Unni now sees the same AC/VBUS-style 5 V condition it would see from USB, so firmware can deliberately pull the Unni out of its battery energy-save behavior.

**3. Real USB is plugged in.** `VBUS` immediately supplies `SYS` through the Schottky/load-share path, so the TPS63031 and ESP are powered from USB rather than discharging the cell. In parallel, the MCP73831 charges `+BATT` at the resistor-programmed current, and the ESP can observe `CHARGE_STAT` as well as the filtered `USB_ADC` divider. USB VBUS also feeds `UNNI_AC` directly through its own Schottky path.

**4. USB always wins over the battery-generated 5 V path.** The forced-awake boost has a hardware VBUS inhibit. When real `VBUS` is present, the MOSFET inhibit network prevents the TPS613222A path from being enabled even if firmware leaves `BOOST_CMD` asserted or crashes in the wrong state. The two 5 V sources therefore do not intentionally drive each other. The output diodes provide the final source isolation at `UNNI_AC`.

**5. USB is removed again.** The charger stops, the battery load-share path retakes `SYS`, and the TPS63031 keeps the ESP on `+3V3` across the source transition. The forced-awake 5 V rail remains off unless firmware explicitly requests it after USB has disappeared. This separation is important: keeping the ESP alive does not automatically force the Unni into its higher-power USB mode.

The practical state table is therefore:

| External USB | `BOOST_CMD` | ESP source | Unni `UNNI_AC` | Result |
| --- | --- | --- | --- | --- |
| absent | 0 | battery -> `SYS` -> TPS63031 | no ESP-generated 5 V | normal battery / energy-save capable |
| absent | 1 | battery -> `SYS` -> TPS63031 | TPS613222A -> `+5V` -> diode | forced-awake / USB-like Unni power state |
| present | 0 | VBUS -> `SYS` -> TPS63031 | VBUS -> diode | USB-powered; battery charging |
| present | 1 | VBUS -> `SYS` -> TPS63031 | VBUS -> diode; boost hardware-inhibited | same safe USB-powered state |

The ADC paths (`BAT_ADC`, `USB_ADC`, `BACKLIGHT_ADC`) and `CHARGE_STAT` let firmware distinguish these power states without making the safety-critical source arbitration depend on software alone.

### Re-generating the README images

With a KiCad 10.99 nightly `kicad-cli` on `PATH`, run:

```sh
./tools/render_readme_assets.sh
```

Or point it at a specific build:

```sh
KICAD_CLI=/path/to/kicad-cli ./tools/render_readme_assets.sh
```

This refreshes all PCB renders and schematic PNGs under `docs/images/`.

## Physical boards

- **USB / power board** — 19 mm fixed width, 1.0 mm finished-board target, USB-C on B.Cu at the measured enclosure datum. It contains USB-C/CC, the TPD2E009DBZR USB ESD shunt, the battery-driven 5 V forced-awake boost and the Unni AC/DC interface.
- **ESP / battery board** — maximum 46 x 32 mm. It contains the ESP32-C6-MINI-1, MCP73831 charger and USB/battery load sharing, TPS63031 3.3 V buck-boost, battery/USB/backlight ADCs, battery NTC, CO2/RT/RH taps, touch emulation, and local service controls.

The boards currently use JST-PH connectors where serviceability is useful. If enclosure clearance proves too tight, their exposed through-hole/SMT pads are also suitable for direct wire soldering; this is an assembly fallback, not a separate electrical architecture.

The 3-pin auxiliary connector **J5** is ordered **pin 1 = `CONN_TOUCH`, pin 2 = `CONN_LED+`, pin 3 = `CONN_BTN`**. `CONN_BTN` goes to ESP32-C6 IO22 (module pin 28); the touch-emulation path couples Q10 to `CONN_TOUCH` through populated C32 = 220 pF.

## Power architecture

```text
USB VBUS ──────────────┬─ MCP73831 (≈196 mA, RPROG=5.1k) ── +BATT
                       ├─ Schottky ── SYS ── TPS63031 ── +3V3 ── ESP32-C6
                       └─ Schottky ─────────────────────── UNNI_AC

protected 1S Li-ion ─ +BATT ─ PMOS load share ─────────── SYS
                    └ +BATT ─ boost switch ─ TPS613222A ─ +5V ─ Schottky ─ UNNI_AC
```

Hardware VBUS inhibit prevents the battery 5 V boost from being enabled while real USB power is present. The battery pack used by the design contains its own protection PCB.

## USB

- USB-C sink: independent 5.1 kΩ Rd on CC1 and CC2.
- Native ESP32-C6 USB Full-Speed is routed through 22 Ω series resistors near the ESP.
- USB ESD: **TI TPD2E009DBZR**, a two-line ground-referenced shunt device with no VBUS/VCC rail. This avoids a clamp path that could back-power VBUS and interfere with the hardware boost inhibit.
- `USB_ADC` includes local RC filtering.
- USB differential geometry is intentionally **not final yet**. Route it only after the selected PCBWay stackup is loaded; final impedance geometry should be checked against PCBWay's impedance/stackup data if controlled impedance is ordered.

## 4-layer PCBWay stackup

The KiCad stackup now models PCBWay's published regular 4-layer **1.0 mm / 1 oz outer / 1 oz inner** construction (70% inner-layer residual-copper variant):

| Layer | KiCad model |
| --- | --- |
| F.Cu | 0.035 mm finished Cu (1 oz) |
| dielectric 1 | 0.1855 mm 7628 RC46% prepreg, εr 4.74 |
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
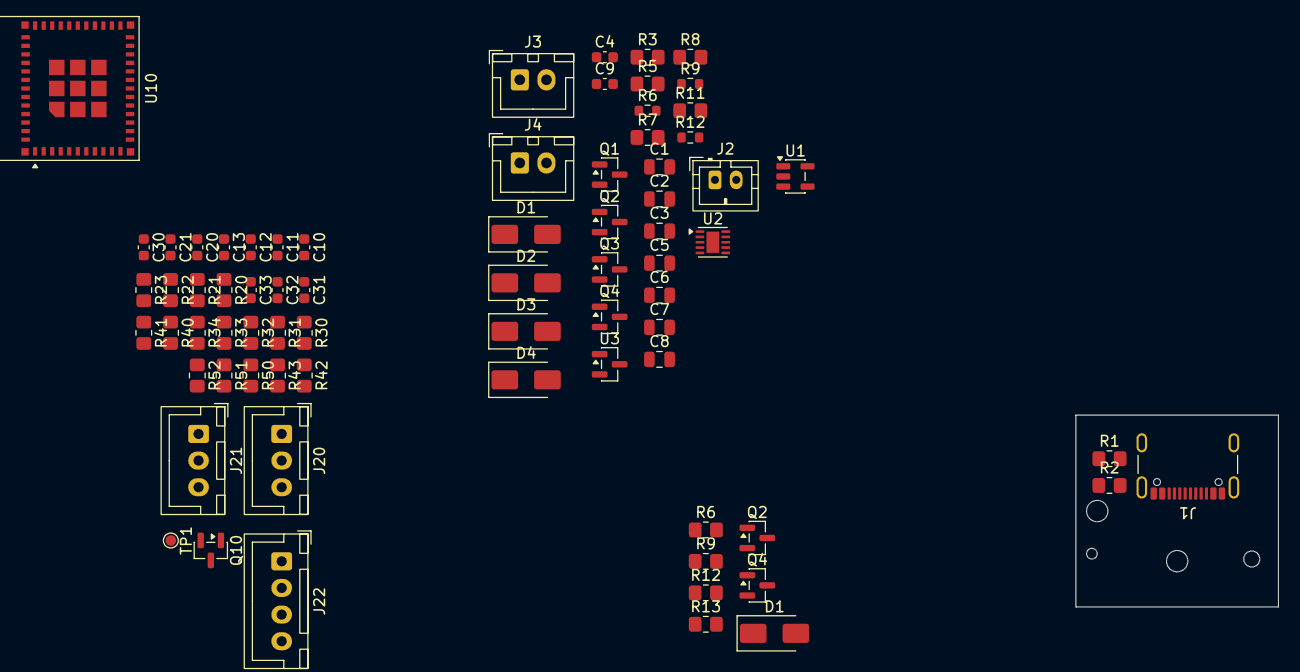
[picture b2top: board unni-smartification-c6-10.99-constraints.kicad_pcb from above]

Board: 2 copper layers, 19.0 x 18.0 mm, 77 parts (0 on the bottom side), 42 nets, no tracks yet.

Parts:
C1, C2: 4.7uF; C_0805_2012Metric
C3, C5, C6, C7: 10uF; C_0805_2012Metric
C4, C11, C20, C21: 100nF; C_0603_1608Metric
C8: 22uF; C_0805_2012Metric
C9: 1uF; C_0603_1608Metric
C10: 10uF; C_0603_1608Metric
C12, C13: 22pF DNP; C_0603_1608Metric
C30: 47pF DNP; C_0603_1608Metric
C31: 100pF DNP; C_0603_1608Metric
C32: 220pF; C_0603_1608Metric
C33: 10nF DNP; C_0603_1608Metric
D1, D1#2, D3, D4: SS14; D_SMA
D2: SS14 DNP; D_SMA
H1: NPTH_2mm; USB_LEFT_MOUNT_D2.0
H2: NPTH_1mm; USB_LEFT_SMALL_D1.0
H3: NPTH_2mm; USB_CENTER_MOUNT_D2.0
H4: NPTH_1.5mm; USB_RIGHT_HOLE_D1.5
J1: UJ20-C-H-G-SMT-1-P16-TR; USB_C_Receptacle_GCT_USB4105-xx-A_16P_TopMnt_Horizontal
J2: B2B-PH-K-S; JST_PH_B2B-PH-K_1x02_P2.00mm_Vertical
J3: B6B-PH-K-S; JST_XH_B2B-XH-A_1x02_P2.50mm_Vertical
J4: S3B-PH-SM4-TB; JST_XH_B2B-XH-A_1x02_P2.50mm_Vertical
J20: CO2 tap: SDA/SCL/GND; JST_XH_B3B-XH-A_1x03_P2.50mm_Vertical
J21: RT/RH tap: RT/RH/GND; JST_XH_B3B-XH-A_1x03_P2.50mm_Vertical
J22: TOUCH / LED+ / LED- / GND; JST_XH_B4B-XH-A_1x04_P2.50mm_Vertical
Q1, Q2, Q2#2: AO3401A; SOT-23
Q3, Q4, Q4#2, Q10: AO3400A; SOT-23
R1, R2, R3: 5.1k; R_0805_2012Metric_Pad1.20x1.40mm_HandSolder
R5, R52: 100k; R_0805_2012Metric_Pad1.20x1.40mm_HandSolder
R6, R9: 1M; R_0603_1608Metric
R6#2, R7, R9#2, R30, R31: 1M; R_0805_2012Metric_Pad1.20x1.40mm_HandSolder
R8, R20, R21, R34, R40, R41, R42, R43: 10k; R_0805_2012Metric_Pad1.20x1.40mm_HandSolder
R11: 150k; R_0805_2012Metric_Pad1.20x1.40mm_HandSolder
R12, R32, R33, R51: 220k; R_0805_2012Metric_Pad1.20x1.40mm_HandSolder
R12#2: 220k; R_0603_1608Metric
R13: 47k; R_0805_2012Metric_Pad1.20x1.40mm_HandSolder
R22, R23: 22R; R_0805_2012Metric_Pad1.20x1.40mm_HandSolder
R50: 330k; R_0805_2012Metric_Pad1.20x1.40mm_HandSolder
TP1: BACKLIGHT_LED_NEG; TestPoint_Pad_D1.0mm
U1: MCP73831; SOT-23-5
U2: TPS63031; WSON-10-1EP_2.5x2.5mm_P0.5mm_EP1.2x2mm
U3: TPS613222A; SOT-23
U10: ESP32-C6-MINI-1-N4; ESP32-C6-MINI-1

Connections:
+3V3: C5.1, C6.1, C10.1, C11.1, R20.1, R21.1, U2.1 (VOUT), U2.10 (FB), U10.3 (3V3)
+5V: C8.1, D2.1 (K), D4.2 (A), U3.1 (VOUT)
+BATT: C2.1, J2.1, J4.1, Q1.3 (D), Q2.2 (S), Q2#2.2 (S), R7.1, R30.1, U1.3 (V_{BAT})
/ESP32-C6 + Auxiliary/BOOT_GPIO9: R21.2, U10.23 (IO9)
/ESP32-C6 + Auxiliary/ESP_EN: R20.2, U10.8 (EN)
/ESP32-C6 + Auxiliary/USB_N: R22.1, U10.17 (IO12)
/ESP32-C6 + Auxiliary/USB_P: R23.1, U10.18 (IO13)
/USB + Power/BOOST_IN: C7.1, Q2.3 (D), Q2#2.3 (D)
BACKLIGHT_ADC: C33.1, R50.2, R51.1, U10.6 (IO3)
BAT_ADC: C20.1, R30.2, R31.1, U10.12 (IO0)
BAT_TEMP_ADC: C21.1, R34.2, U10.5 (IO2)
BAT_TEMP_EXCITE: R34.1, U10.29 (IO23)
BOOST_CMD: R8.1, U10.27 (IO21)
CHARGE_STAT: R11.2, R12.1, U10.19 (IO14)
CO2_SCL: R41.2, U10.25 (IO19)
CO2_SDA: R40.2, U10.24 (IO18)
GND: C1.2, C2.2, C3.2, C4.2, C5.2, C6.2, C7.2, C8.2, C9.2, C10.2, C11.2, C12.2, C13.2, C20.2, C21.2, C33.2, J1.A1 (GND), J1.A12 (GND), J1.B1 (GND), J1.B12 (GND), J1.SH (SHIELD), J2.2, J3.2, J4.2, J20.3, J21.3, J22.4, Q3.2 (S), Q4.2 (S), Q4#2.2 (S), Q10.2 (S), R1.2, R2.2, R3.2, R6.2, R6#2.1, R9.2, R9#2.2, R12.2, R12#2.2, R13.1, R31.2, R33.2, R51.2, R52.2, U1.2 (V_{SS}), U2.3 (PGND), U2.7 (PS/SYNC), U2.9 (GND), U2.11 (PGND), U3.3 (GND), U10.1 (GND), U10.2 (GND), U10.11 (GND), U10.14 (GND), U10.36 (GND), U10.37 (GND), U10.38 (GND), U10.39 (GND), U10.40 (GND), U10.41 (GND), U10.42 (GND), U10.43 (GND), U10.44 (GND), U10.45 (GND), U10.46 (GND), U10.47 (GND), U10.48 (GND), U10.49 (GND), U10.50 (GND), U10.51 (GND), U10.52 (GND), U10.53 (GND)
unnamed: D2.2 (A), U3.2 (SW)
unnamed: J1.A5 (CC1), R1.1
unnamed: J1.B5 (CC2), R2.1
unnamed: J20.1, R40.1
unnamed: J20.2, R41.1
unnamed: J21.1, R42.1
unnamed: J21.2, R43.1
unnamed: C30.1, C31.1, C32.1, J22.1
unnamed: J22.2, R50.1
unnamed: J22.3, TP1.1 (1_1)
unnamed: Q1.1 (G), R5.2, R6#2.2
unnamed: Q2.1 (G), Q2#2.1 (G), Q3.3 (D), R7.2
unnamed: Q3.1 (G), Q4.3 (D), Q4#2.3 (D), R8.2, R9#2.1
unnamed: C30.2, C31.2, C32.2, Q10.3 (D)
unnamed: R3.1, U1.5 (PROG)
unnamed: R11.1, U1.1 (STAT)
RH: R43.2, U10.16 (IO7)
RT: R42.2, U10.15 (IO6)
SYS: C3.1, C4.1, D1#2.1 (K), Q1.2 (S), Q4.1 (G), U2.5 (VIN), U2.6 (EN), U2.8 (VINA)
TOUCH_TRIGGER: Q10.1 (G), R52.1, U10.26 (IO20)
UNNI_AC: C9.1, D3.1 (K), D4.1 (K), J3.1
USB_ADC: R32.2, R33.1, U10.13 (IO1)
USB_RAW_N: C12.1, J1.A7 (D-), J1.B7 (D-), R22.2
USB_RAW_P: C13.1, J1.A6 (D+), J1.B6 (D+), R23.2
VBUS: C1.1, D1#2.2 (A), D3.2 (A), J1.A4 (VBUS), J1.A9 (VBUS), J1.B4 (VBUS), J1.B9 (VBUS), Q4#2.1 (G), R5.1, R13.2, R32.1, U1.4 (V_{DD})

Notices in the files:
README.md:
Project-authored code and documentation are licensed under:
GPL-3.0-or-later
See [LICENSE](LICENSE).
Referenced or adapted Sensirion-compatible portions retain the required upstream notices and provenance information.
See: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
